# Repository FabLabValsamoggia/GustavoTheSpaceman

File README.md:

# Gustavo the Spaceman

developed with ♥ by FabLab Valsamoggia

**Gustavo the spaceman** is an educational puppet kit that can help educators and teachers to teach and experiment 3D printing, electronics and coding with children. Students can customize the puppet by adding details and tools using a 3D modeling software. Then with Arduino IDE and Blockly they can program lights and sounds to create their own character. The kit is made of a 3D printed puppet with some holes for additional parts, one Arduino Nano with USB cable, a shield with 16 LEDs and 4 buttons, a small speaker and a miniSD card reader to upload sounds.

## Contributing
Pull requests are welcome. For major changes, please open an issue first to discuss what you would like to change.

Please make sure to update tests as appropriate.

## License
[MIT](https://choosealicense.com/licenses/mit/)

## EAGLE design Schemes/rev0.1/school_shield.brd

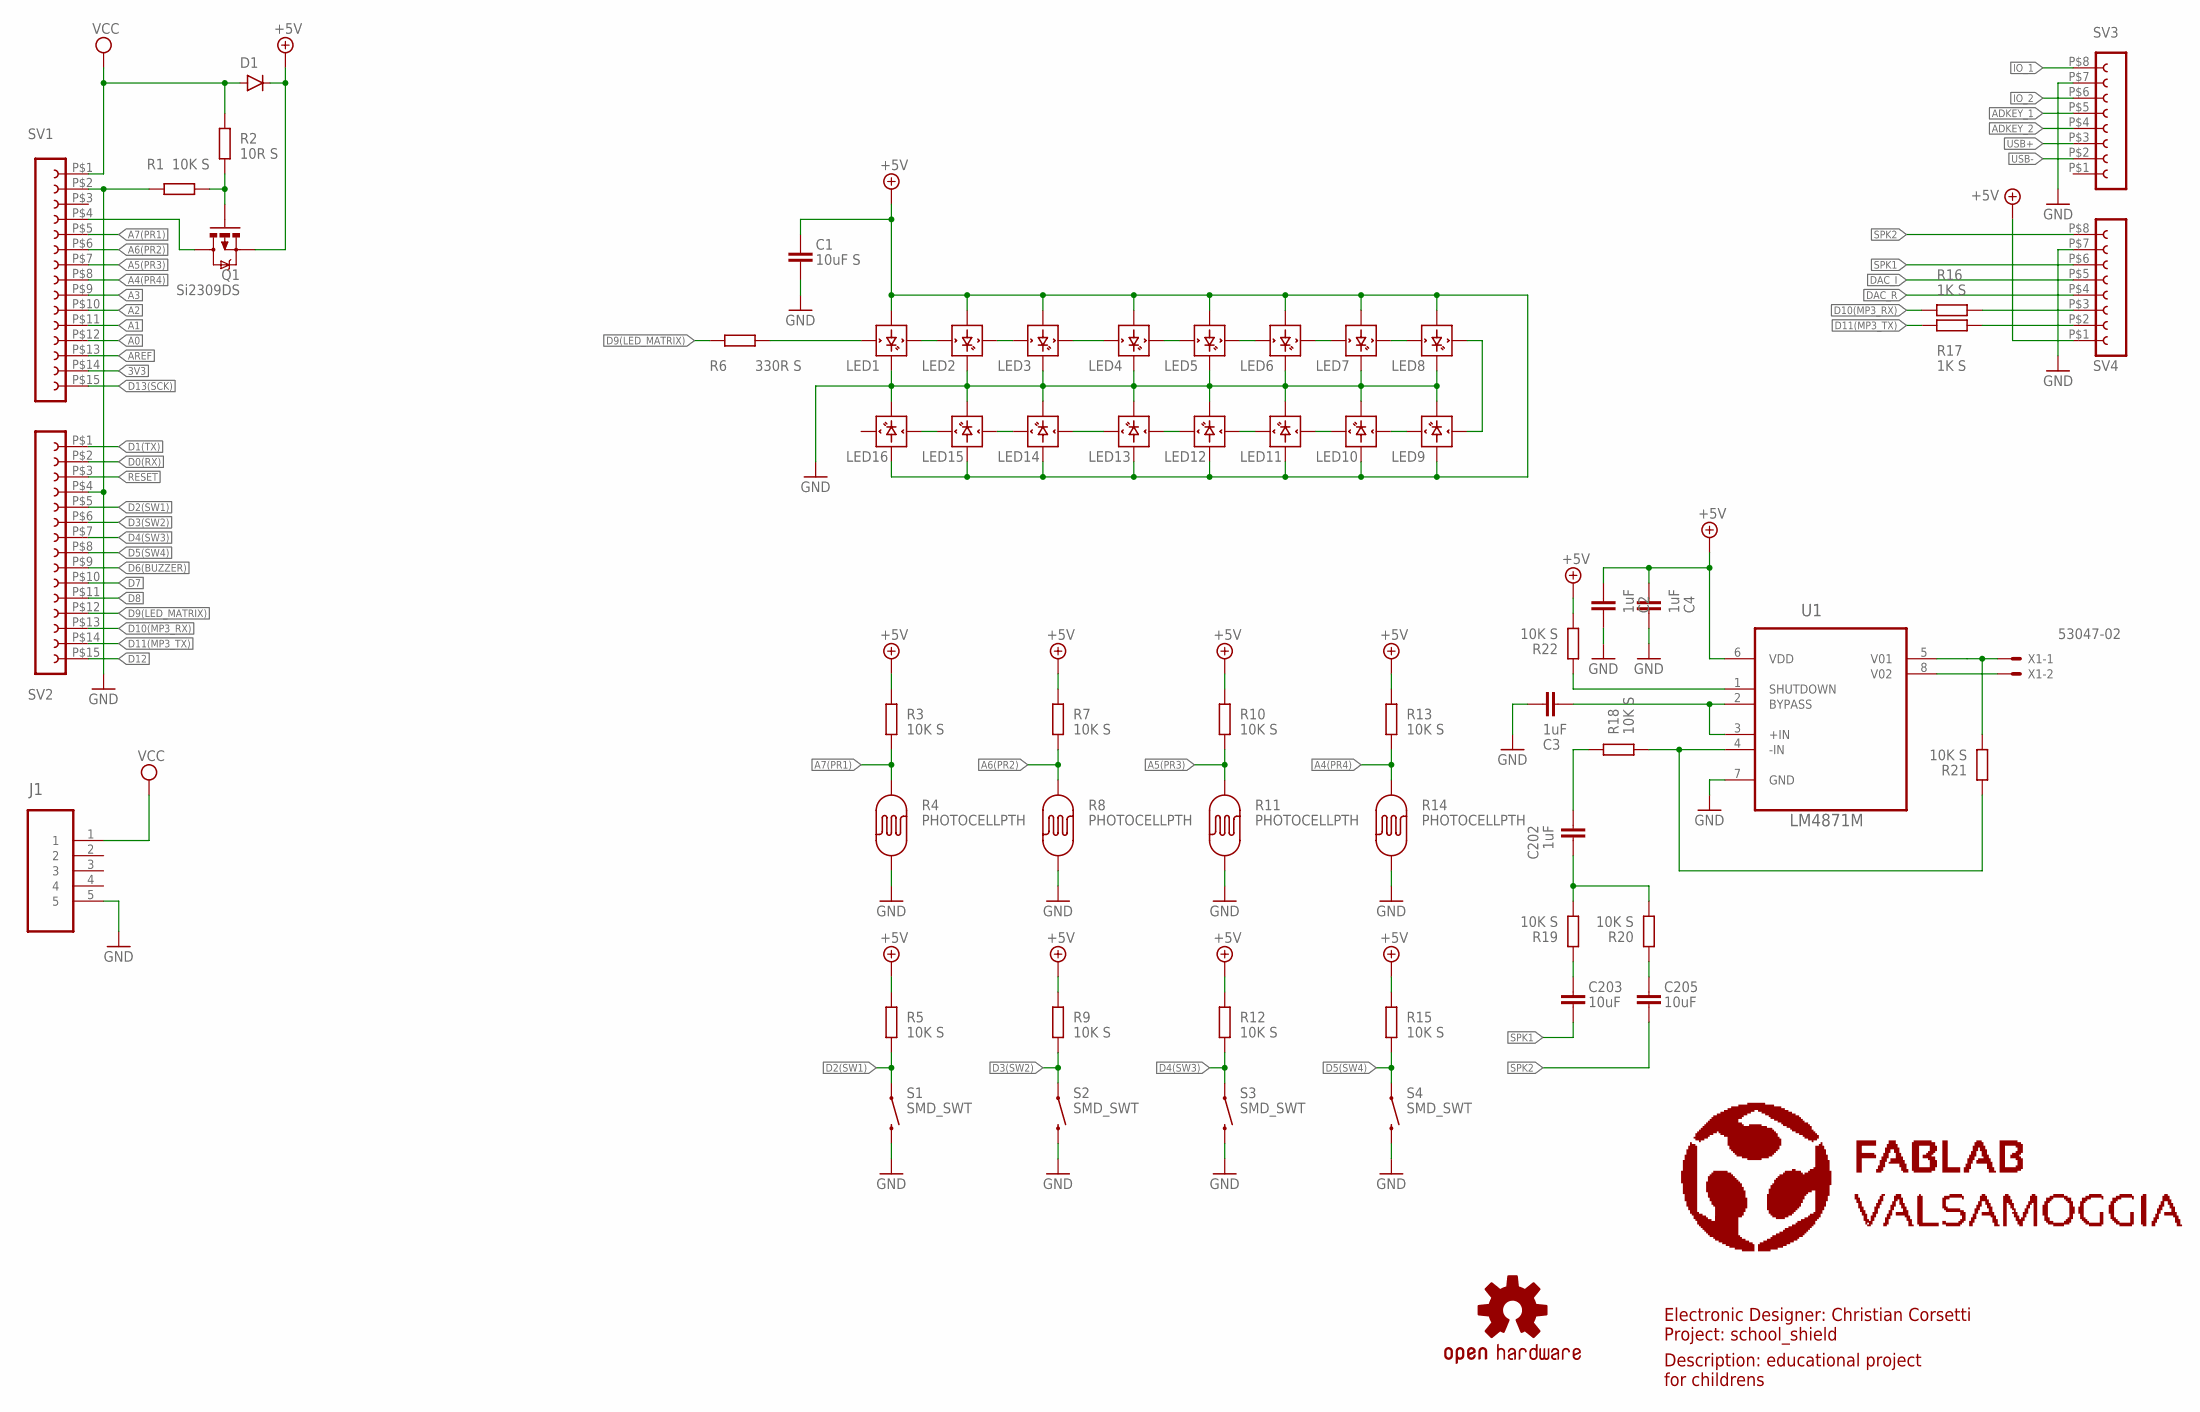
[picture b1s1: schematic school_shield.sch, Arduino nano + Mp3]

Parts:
C1: 10uF S; C0805
C2, C3, C4, C202: 1uF; C0805
C203, C205: 10uF; C0805
D1: DIODESMA; SMA-DIODE
J1: 47346-0001; MOLEX_47346-0001
LED1, LED2, LED3, LED4, LED5, LED6, LED7, LED8, LED9, LED10, LED11, LED12, LED13, LED14, LED15, LED16: WS2812B_ALT; WS2812B
LOGO1: OSHW-LOGOMINI; OSHW-LOGO-MINI
Q1: Si2309DS; SOT23-3
R1, R3, R5, R7, R9, R10, R12, R13, R15, R18, R19, R20, R21, R22: 10K S; R0805
R2: 10R S; R0805
R4, R8, R11, R14: PHOTOCELLPTH; PHOTOCELL
R6: 330R S; R0805
R16, R17: 1K S; R0805
S1, S2, S3, S4: SMD_SWT; TACTILE_SWITCH_TALL
SV1, SV2: FE15-1SMD; FE15_SMD
SV3, SV4: FE08-1SMD; FE08_SMD
U1: LM4871M; SOIC127P600X175-8N
U$1: FABLAB
X1: 53047-02

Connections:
3V3: SV1.P$14 (14)
+5V: C1.2, C2.1, C4.1, D1.C, LED1.1-VDD (VDD), LED2.1-VDD (VDD), LED3.1-VDD (VDD), LED4.1-VDD (VDD), LED5.1-VDD (VDD), LED6.1-VDD (VDD), LED7.1-VDD (VDD), LED8.1-VDD (VDD), LED9.1-VDD (VDD), LED10.1-VDD (VDD), LED11.1-VDD (VDD), LED12.1-VDD (VDD), LED13.1-VDD (VDD), LED14.1-VDD (VDD), LED15.1-VDD (VDD), LED16.1-VDD (VDD), Q1.2 (S), R3.2, R5.2, R7.2, R9.2, R10.2, R12.2, R13.2, R15.2, R22.1, SV4.P$1 (1), U1.6 (VDD)
A0: SV1.P$12 (12)
A1: SV1.P$11 (11)
A2: SV1.P$10 (10)
A3: SV1.P$9 (9)
A4(PR4): R13.1, R14.2, SV1.P$8 (8)
A5(PR3): R10.1, R11.2, SV1.P$7 (7)
A6(PR2): R7.1, R8.2, SV1.P$6 (6)
A7(PR1): R3.1, R4.2, SV1.P$5 (5)
ADKEY_1: SV3.P$5 (5)
ADKEY_2: SV3.P$4 (4)
AREF: SV1.P$13 (13)
AUDIO: R18.1, R21.2, U1.4 (-IN)
D0(RX): SV2.P$2 (2)
D1(TX): SV2.P$1 (1)
D2(SW1): R5.1, S1.A2 (1), SV2.P$5 (5)
D3(SW2): R9.1, S2.A2 (1), SV2.P$6 (6)
D4(SW3): R12.1, S3.A2 (1), SV2.P$7 (7)
D5(SW4): R15.1, S4.A2 (1), SV2.P$8 (8)
D6(BUZZER): SV2.P$9 (9)
D7: SV2.P$10 (10)
D8: SV2.P$11 (11)
D9(LED_MATRIX): R6.2, SV2.P$12 (12)
D10(MP3_RX): R16.2, SV2.P$13 (13)
D11(MP3_TX): R17.2, SV2.P$14 (14)
D12: SV2.P$15 (15)
D13(SCK): SV1.P$15 (15)
DAC_I: SV4.P$5 (5)
DAC_R: SV4.P$4 (4)
GND: C1.1, C2.2, C3.2, C4.2, J1.5, LED1.3-GND (GND), LED2.3-GND (GND), LED3.3-GND (GND), LED4.3-GND (GND), LED5.3-GND (GND), LED6.3-GND (GND), LED7.3-GND (GND), LED8.3-GND (GND), LED9.3-GND (GND), LED10.3-GND (GND), LED11.3-GND (GND), LED12.3-GND (GND), LED13.3-GND (GND), LED14.3-GND (GND), LED15.3-GND (GND), LED16.3-GND (GND), R1.2, R4.1, R8.1, R11.1, R14.1, S1.B2 (2), S2.B2 (2), S3.B2 (2), S4.B2 (2), SV1.P$2 (2), SV2.P$4 (4), SV3.P$7 (7), SV4.P$7 (7), U1.7 (GND)
IO_1: SV3.P$8 (8)
IO_2: SV3.P$6 (6)
unnamed: Q1.1 (G), R1.1, R2.2
unnamed: C3.1, U1.2 (BYPASS), U1.3 (+IN)
unnamed: Q1.3 (D), SV1.P$4 (4)
unnamed: LED1.4-DIN (DIN), R6.1
unnamed: C205.1, R20.2
unnamed: C203.1, R19.2
unnamed: C202.1, R19.1, R20.1
unnamed: R22.2, U1.1 (SHUTDOWN)
unnamed: R21.1, U1.5 (V01), X1.1
unnamed: C202.2, R18.2
unnamed: U1.8 (V02), X1.2
unnamed: LED1.2-DOUT (DOUT), LED2.4-DIN (DIN)
unnamed: LED2.2-DOUT (DOUT), LED3.4-DIN (DIN)
unnamed: LED3.2-DOUT (DOUT), LED4.4-DIN (DIN)
unnamed: LED4.2-DOUT (DOUT), LED5.4-DIN (DIN)
unnamed: LED5.2-DOUT (DOUT), LED6.4-DIN (DIN)
unnamed: LED6.2-DOUT (DOUT), LED7.4-DIN (DIN)
unnamed: LED7.2-DOUT (DOUT), LED8.4-DIN (DIN)
unnamed: LED8.2-DOUT (DOUT), LED9.4-DIN (DIN)
unnamed: LED9.2-DOUT (DOUT), LED10.4-DIN (DIN)
unnamed: LED10.2-DOUT (DOUT), LED11.4-DIN (DIN)
unnamed: LED11.2-DOUT (DOUT), LED12.4-DIN (DIN)
unnamed: LED12.2-DOUT (DOUT), LED13.4-DIN (DIN)
unnamed: LED13.2-DOUT (DOUT), LED14.4-DIN (DIN)
unnamed: LED14.2-DOUT (DOUT), LED15.4-DIN (DIN)
unnamed: LED15.2-DOUT (DOUT), LED16.4-DIN (DIN)
unnamed: R16.1, SV4.P$3 (3)
unnamed: R17.1, SV4.P$2 (2)
RESET: SV2.P$3 (3)
SPK1: C203.2, SV4.P$6 (6)
SPK2: C205.2, SV4.P$8 (8)
USB+: SV3.P$3 (3)
USB-: SV3.P$2 (2)
VCC: D1.A, J1.1, R2.1, SV1.P$1 (1)

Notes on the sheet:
Electronic Designer: Christian Corsetti Project: school_shield
Description: educational project for childrens

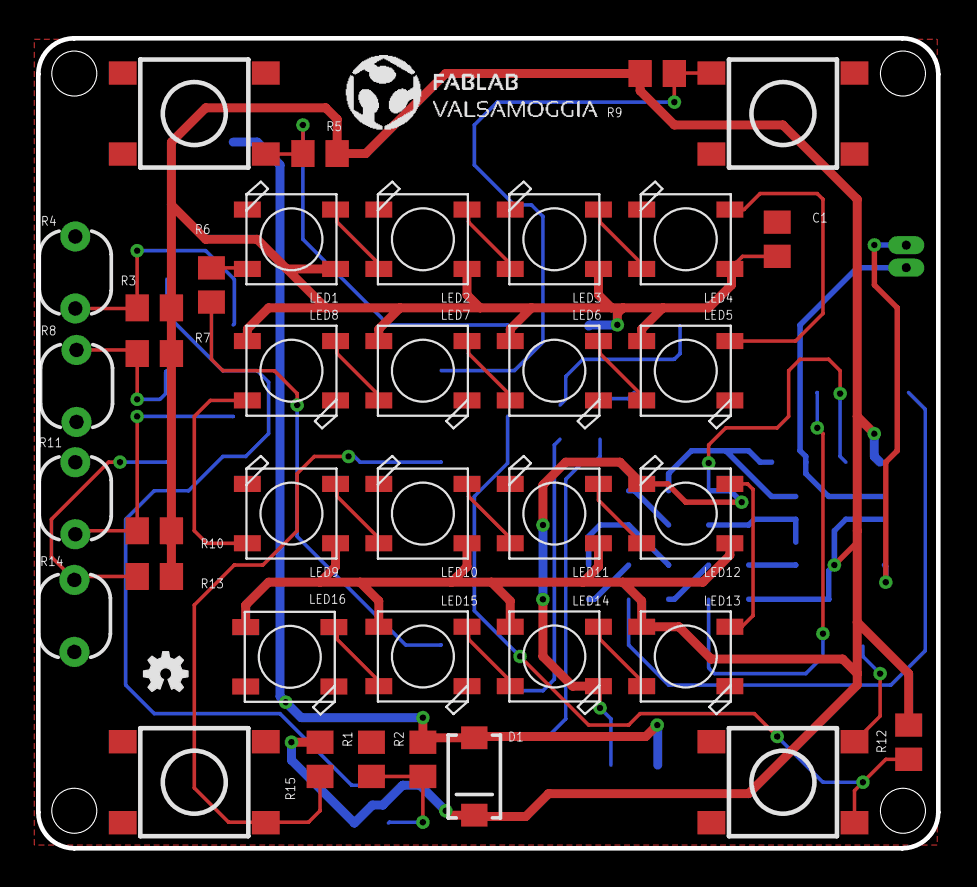
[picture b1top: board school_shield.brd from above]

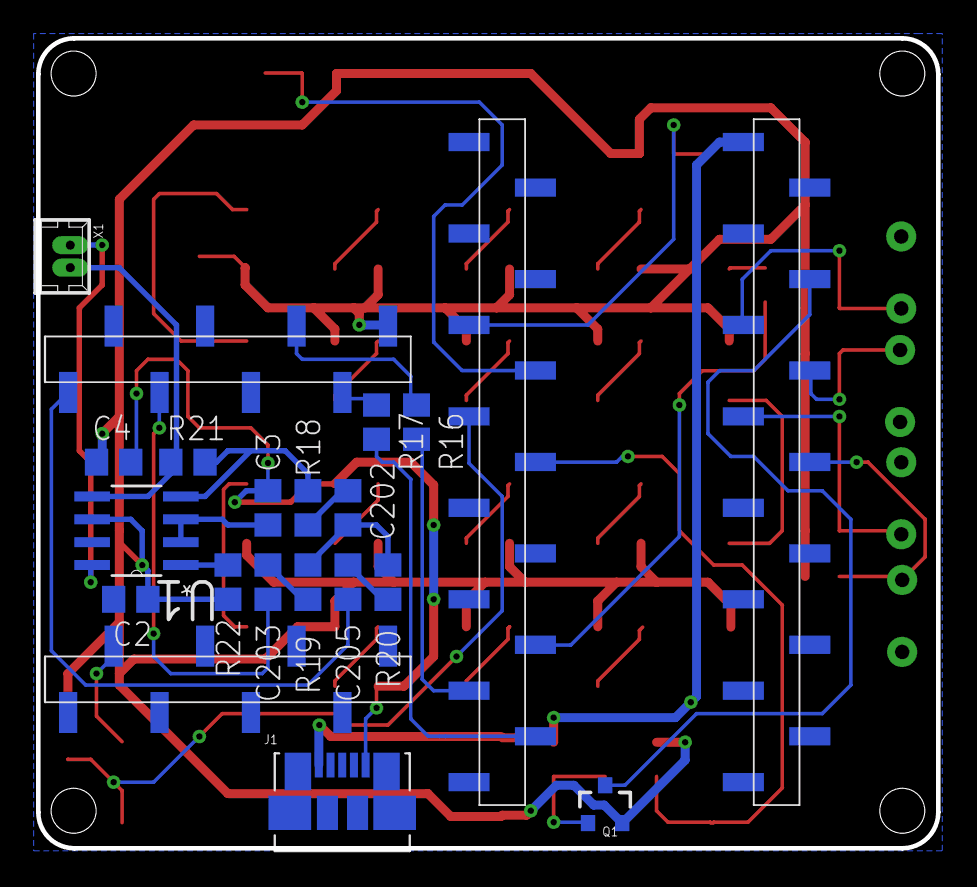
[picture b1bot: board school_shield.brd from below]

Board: 2 copper layers, 50.0 x 45.0 mm, 60 parts (21 on the bottom side), 45 nets.

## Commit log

2020-09-24 add logo
2020-09-24 add some cool informations
2020-09-24 add gustavo body
2020-10-15 move folder for arduino IDE building
2020-10-15 bug fixe: add btns_check_state
